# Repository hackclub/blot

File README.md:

# Blot, the plotter bot from Hack Club

**[🕸 Landing Page](https://blot.hackclub.com)** | **[💻 Online Editor](https://blot.hackclub.com/editor)** | **[👀 Gallery](https://blot.hackclub.com/gallery)**

> Saw Blot at [RMRRF](https://rmrrf.com) 2026? That was a fork of the firmware, check it out [here](https://github.com/samdev-7/upgraded-blot).

Create programmatic art in our web-based editor and submit it to the gallery and we'll send you a CNC machine which can make that art for free.
Blot is a [**You Ship, We Ship**](https://github.com/hackclub/blot/tree/main?tab=readme-ov-file#you-ship-we-ship) project from [Hack Club](https://hackclub.com).

> Everything about Blot is open source. The online editor and drawing library can be freely used by anyone, and we encourage all to submit to the gallery through PRs! However, you must be a teenager or younger to receive a free machine.

A piece of art made for Blot can be the first program you ever write, but it can also be a challenge for a master programmer. Check out some of the art made already in our [gallery](https://blot.hackclub.com/gallery). Every piece of art you see is actually a program. Many of them create unique pieces every time the art is run. You may be looking at an artwork which has never been seen before, even by the creator.

For a short video introduction to Blot [check out our 38 second trailer](https://www.youtube.com/watch?v=d1noJNmfvC0).

# How It Works

### 1) Create a piece of programmatic art in the web editor.

To learn the Blot drawing library follow our [getting started guide](https://blot.hackclub.com/editor?guide=start). Check out the examples in the [gallery](https://blot.hackclub.com/gallery) and then follow along with some of our [guides](https://blot.hackclub.com/guides).

### 2) Submit that art to the public gallery.

The [submission rules to get a Blot for a PR are here](https://github.com/hackclub/blot/blob/main/docs/GET_A_BLOT.md). **You must be a teenager (or younger to qualify for a free machine)** but anyone can make art and make a PR.

### 3) Receive the parts to build your own Blot that can draw that art in real life.

The [bill of materials can be found here](/docs/BOM.toml) and an [assembly guide here](https://blot.hackclub.com/assembly).

<!--  -->

# Blot is...

**A custom CNC drawing machine** designed from scratch to introduce you to digital fabrication.
It's made of 6 unique 3D printed parts with a custom control board and easy to understand firmware, which can be interfaced with through JavaScript in the browser.
Blot is designed in OnShape. Check out the [3D model of the project](https://cad.onshape.com/documents/536478c2ac00624edd8e2182/w/945ceabd15096661108b7650/e/61fd4346c9fdab983c6ba24d?renderMode=0&uiState=66980ee799bd766f406eb9c8).
You can find the [bill of materials here](https://blot.hackclub.com/assembly) and, if you'd like to 3D print your Blot, [the parts are here](https://github.com/hackclub/blot/tree/main/hardware/mechanical/drawing-thing-v4). The entire build costs about $150 dollars. If you're a teen we will give you all the parts for a PR with your an art piece you coded yourself.

**A web based editor for programmatic art** that we designed specifically for pen plotting with a [custom geometry library](/docs/DOCUMENTATION.md).
We practiced programmatic pen plotting with [some](https://github.com/LingDong-) [amazing artists](https://static1.squarespace.com/static/63fbc39db5b01b5fa30423db/t/649b424d33b2ce3e0d5b63a5/1687896656015/June+Cohort+Zine.pdf).
There is so much to learn and explore on the programming and the aesthetic side.

# Blot Docs

Here are a collection of resources for Blot:

- [Complete documentation of the drawing library in the editor](https://github.com/hackclub/blot/blob/main/docs/DOCUMENTATION.md)
- [Short documentation shown in the Blot editor](https://github.com/hackclub/blot/blob/main/public/TOOLKIT.md)
- [The Blot assembly and operation guide](https://github.com/hackclub/blot/blob/main/docs/assembly/ASSEMBLY.md)
- [The source of truth bill of materials (BOM)](https://github.com/hackclub/blot/blob/main/docs/BOM.toml)
- [Criteria for how to get a Blot and a guide on how to submit a PR](https://github.com/hackclub/blot/blob/main/docs/GET_A_BLOT.md)
- [A guide on how to review Blot submissions](https://github.com/hackclub/blot/blob/main/docs/BLOT_REVIEW.md)
- [A brief guide on how to approve Blot requests for Blot shipments](https://github.com/hackclub/blot/blob/main/docs/APPROVING_BLOT_REQUESTS.md)
- [Information on how we order Blot supplies from our manufacturing partners](https://github.com/hackclub/blot/blob/main/docs/ORDERING_BLOT_KITS.md)
- [The files for the 3D printed parts](https://github.com/hackclub/blot/tree/main/hardware/mechanical/blot-v6)
- [The source files for the control PCB](https://github.com/hackclub/blot/tree/main/hardware/motor-control-board/circuit/controller)
- [The source files for the power delivery PCB](https://github.com/hackclub/blot/tree/main/hardware/motor-control-board/circuit/power-delivery)
- [The firmware for the Blot control board](https://github.com/hackclub/blot/blob/main/hardware/motor-control-board/firmware/firmware.ino)
- [Sample Blot based lesson plan](https://github.com/hackclub/blot/blob/main/docs/lesson/LESSON-PLAN.md)
- [Video of a Blot being assembled](https://www.youtube.com/watch?v=7N-Nu6_oo4I)
- [Video of operating a Blot](https://www.youtube.com/watch?v=qDP5CNjFHJE)
- [Video of making a Blot submission](https://www.youtube.com/watch?v=AmbjNEPuv14)
- [Video Blot promo trailer](https://www.youtube.com/watch?v=d1noJNmfvC0)
- [Video introduction to JavaScript in the context of Blot](https://www.youtube.com/watch?v=3KAan1PzmxA)
- [Video introduction to Blot editor](https://www.youtube.com/watch?v=OZ9KaFr1V_o)
- [Video demonstrating working through a Blot guide](https://www.youtube.com/watch?v=mP4rUdaF8ng)

# What are People Making with Blot

Blot has been in development since January 2023 and was released April 2024. We've had lots of people use the Blot editor and the Blot machine to create visual art, run workshops and as part of interactive installations. Here's a sense of what can be done with Blot.

### Programmatic Art

There are all sorts of styles of programmatic art. Here are some examples of great Blot submissions that show a range of styles. This list is by no means exhaustive.

**The natural scene** is a common source of artistic inspiration. This could be called figurative or representational art when it tries to depict a real thing with some fidelity. One example are these roots by Kai (age 17).

**The geometric pattern** is natural avenue to pursue when making art with computers because code is a great way to describe patterns. Oz's approach of clipping overlapping segments creates a wonderful sense of depth.

**The tech demo (with composition)** is focusing on a specific technical approach like in Henry's (age 15) ray marcher. The art piece isn't complete though until the artists uses the technique to make a composition.

<a href="https://blot.hackclub.com/editor?src=https://raw.githubusercontent.com/hackclub/blot/main/art/raymarching-henry/index.js">
  <picture>
    <source media="(prefers-color-scheme: dark)" srcset="https://github.com/hackclub/blot/assets/61765149/d65464eb-8cc2-4bf3-be82-0b4cc12070bd">
    <source media="(prefers-color-scheme: light)" srcset="https://github.com/hackclub/blot/assets/27078897/90c01a52-0404-423f-8ae9-763bc591ff9f">
    
  </picture>
</a>

**The data transformation** can be seen in Kieran's (age 15) self portrait. It takes data from an SVG but modifies it programmatically to produce an art piece. This approach could be used to visualize data that may not of been visual to begin with.

**The concept** is important with any artwork and can be mixed with any of the genres above. Ultimately an interesting idea can be what elevates something that is visually pretty simple, one example by Ayush is the Blot's own self portrait.

<a href="https://blot.hackclub.com/editor?src=https://raw.githubusercontent.com/hackclub/blot/main/art/blot-ayush/index.js">
  <picture>
    <source media="(prefers-color-scheme: dark)" srcset="https://github.com/hackclub/blot/assets/61765149/12044cdf-a498-438c-814b-48622488e42f">
    <source media="(prefers-color-scheme: light)" srcset="https://github.com/hackclub/blot/assets/27078897/1f367d9b-aa74-4fca-8623-259a06800335">
    
  </picture>
</a>

For way more examples check out the [gallery](https://blot.hackclub.com/gallery).

### Blot as Creative Material

You ship we ship projects are developed to provide technological creative material. The Blot was developed to not just create visual programs on computers but also to explore robotic and interactive technology. Here are some ways the machine or project has been used to create interactive technology experiences.

[**Lineflow**](https://github.com/leomcelroy/lineflow) was developed as an interactive art piece for an MIT Museum event. Participants would create a single line drawing on the computer and would then watch a simulation of a line folding into their drawing. Three frames of that simulation were strung together to create a timeline of the animation that would be drawn by a Blot to be brought home by the participant.

**The infinite gallery** at [Outernet](https://www.youtube.com/watch?v=O1s5HqSqKi0) (Hack Club's 2023 summer hackathon). Leo, Kai, and Henry constructed a black out box that contained an infinite art gallery. Participant's entered a room sized black box with one wall illuminated with artwork and a giant joystick in the center. They could navigate the gallery with the joystick and as they explored new (possibly never before seen) art was generated based on their location.

**Chinese calligraphy workshop** was developed for and run at the [Hack Club leader summit 2024](https://www.youtube.com/watch?v=UZEm5lONg7g) by Bright Li (age 15). During it participants learned how to draw Chinese calligraphy programmatically and then handed ink brushes to Bright's Blot robot to put the drawings to the page.

# It's All Open Source

Every part of Blot is freely available for you to investigate and discover.
That includes the editor, the hardware design, the electronics, and even the finances around the project.
We think people deserve tools they can take ownership of. That's why we give away the source for free.

Our projects at Hack Club have hundreds of teenage contributors from all over the world. If you want to learn how to program, we invite you to jump in and start building tools used by thousands.

You're also welcome to participate and use our tools if you aren't a teen (like making art or building your own blot), but our [online community](https://hackclub.com/slack) is for teens only.

# You Ship, We Ship

At Hack Club we're reimagining a new type of public education for technology. We believe people learn best by creating things they care about and sharing them with others. We build open source creative tools with young people all around the world. These tools are gateways to new subjects in technology like [embedded systems](https://sprig.hackclub.com), [circuits](https://onboard.hackclub.com) or digital fabrication robotics. When teenagers build things with our tools we send them more creative materials for free.

Our goal is to build a new type of library online that offers learners not just media to consume but tools to create. And it is free and open source to all. We're just getting started...

# Development

Join the `#blot` channel on the [Hack Club Slack](https://hackclub.com/slack).

The Blot editor is run with an Express server.

After installing `Git`, `Node.js`, and `Yarn`, clone the repo.

```
git clone https://github.com/hackclub/blot/
yarn install
```

To run the development server:

```
yarn dev
```

# License

The Hack Club Blot is open source and licensed under the [MIT License](https://github.com/hackclub/blot/LICENSE.md). Fork, remix, and make it your own! Pull requests and other contributions greatly appreciated.

# Acknowledgements

Many people have contributed to Blot, to mention a few and give much thanks too...

MIT's Center for Bits and Atoms for providing expert advice and occasionally a space to work.

Sam Hu and his team at ISourceAsia for supplying Blot parts and becoming a critical part of the Blot team.

Paul Hamilton for his contributions to embedded circuit designs.

Oz Nova for writing an excellent getting started guide.

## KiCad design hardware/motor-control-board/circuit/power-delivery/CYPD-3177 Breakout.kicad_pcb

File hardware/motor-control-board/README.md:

# Blot Control Board

The assembled blot control board is a main board with a set of smaller boards attached to it's headers:

- 1x Blot Control Board ([designed in house](./circuit/controller/))
    - 2x A4988 stepper motor drivers
    - 1x Seeeduino XIAO RP2040
    - 1x USB-C Power Delivery board ([designed in house](./circuit/power-delivery/))
    - 1x Stepper motor breakout board ([designed in house](./circuit/stepper-motor-headers/))

The KiCAD project files are provided in the repo and are designed with KiCAD v7. This may not be compatible with previous versions, but you can get the latest version [here](https://www.kicad.org/download/). 

## Carrier Board

The carrier board wires the breakouts together, provides external power circuitry for the A4988 and steppers, and a convenient way to mount the board to the blot machine. It's a simple 2-layer 1.6mm PCB measured at 50x70mm. It also has a pin header breaking out 5 unused GPIO pins, including 1 DAC channel, 2 analog-capable pins, and one I2C bus. 

## Power Delivery Board

The power delivery board provides a fixed output of 9V1A using the CYPD3177 chipset. It's highly flexible, allowing USB-C Charging up to 15W and USB-C PD up to 100W. Unlike many other chips available, it does not require any firmware nor flashing, and power settings are configured with pullup and pulldown resistors. This board is set to 9V @ 1A, to ensure maximum compatibility with most PD-capable bricks. It's very compact, measuring less than 22x32mm with breadboard-friendly mounting, an affordable 2-layer design, and single side SMD component placement. 

During prototyping, we used an off-the-shelf module from Amazon. These only had four 2.54mm pins on the edge of the board and were hard to mount onto the board securely. Building our own also gave us better control over supply of these boards. 

*As a precaution: while this board is breadboard friendly, typical solderless breadboards are only rated up to _5V @ 1A_. Do _not_ use this on a solderless breadboard.*

## Additional Relevant Reading

Below is a list of datasheets / product briefs that may be relevant. 

[Seeeduino RP2040 XIAO](https://wiki.seeedstudio.com/XIAO-RP2040/)\
[A4988 Breakout Board](https://www.pololu.com/product/1182)\
[CYPD3177](https://www.infineon.com/cms/en/product/universal-serial-bus/usb-c-charging-port-controllers/ez-pd-barrel-connector-replacement-bcr/cypd3177-24lqxq/)\
[DMP3013SFV](https://www.diodes.com/assets/Datasheets/DMP3013SFV.pdf)\
[MM3Z15VC](https://www.onsemi.com/pdf/datasheet/mm3z9v1c-d.pdf)\
[WCAP-ATG5](https://www.we-online.com/components/products/datasheet/860020573008.pdf)\
[JS Series Switch](https://www.ckswitches.com/media/1422/js.pdf)\
[Schottky Diode](https://datasheets.kyocera-avx.com/schottky.pdf)

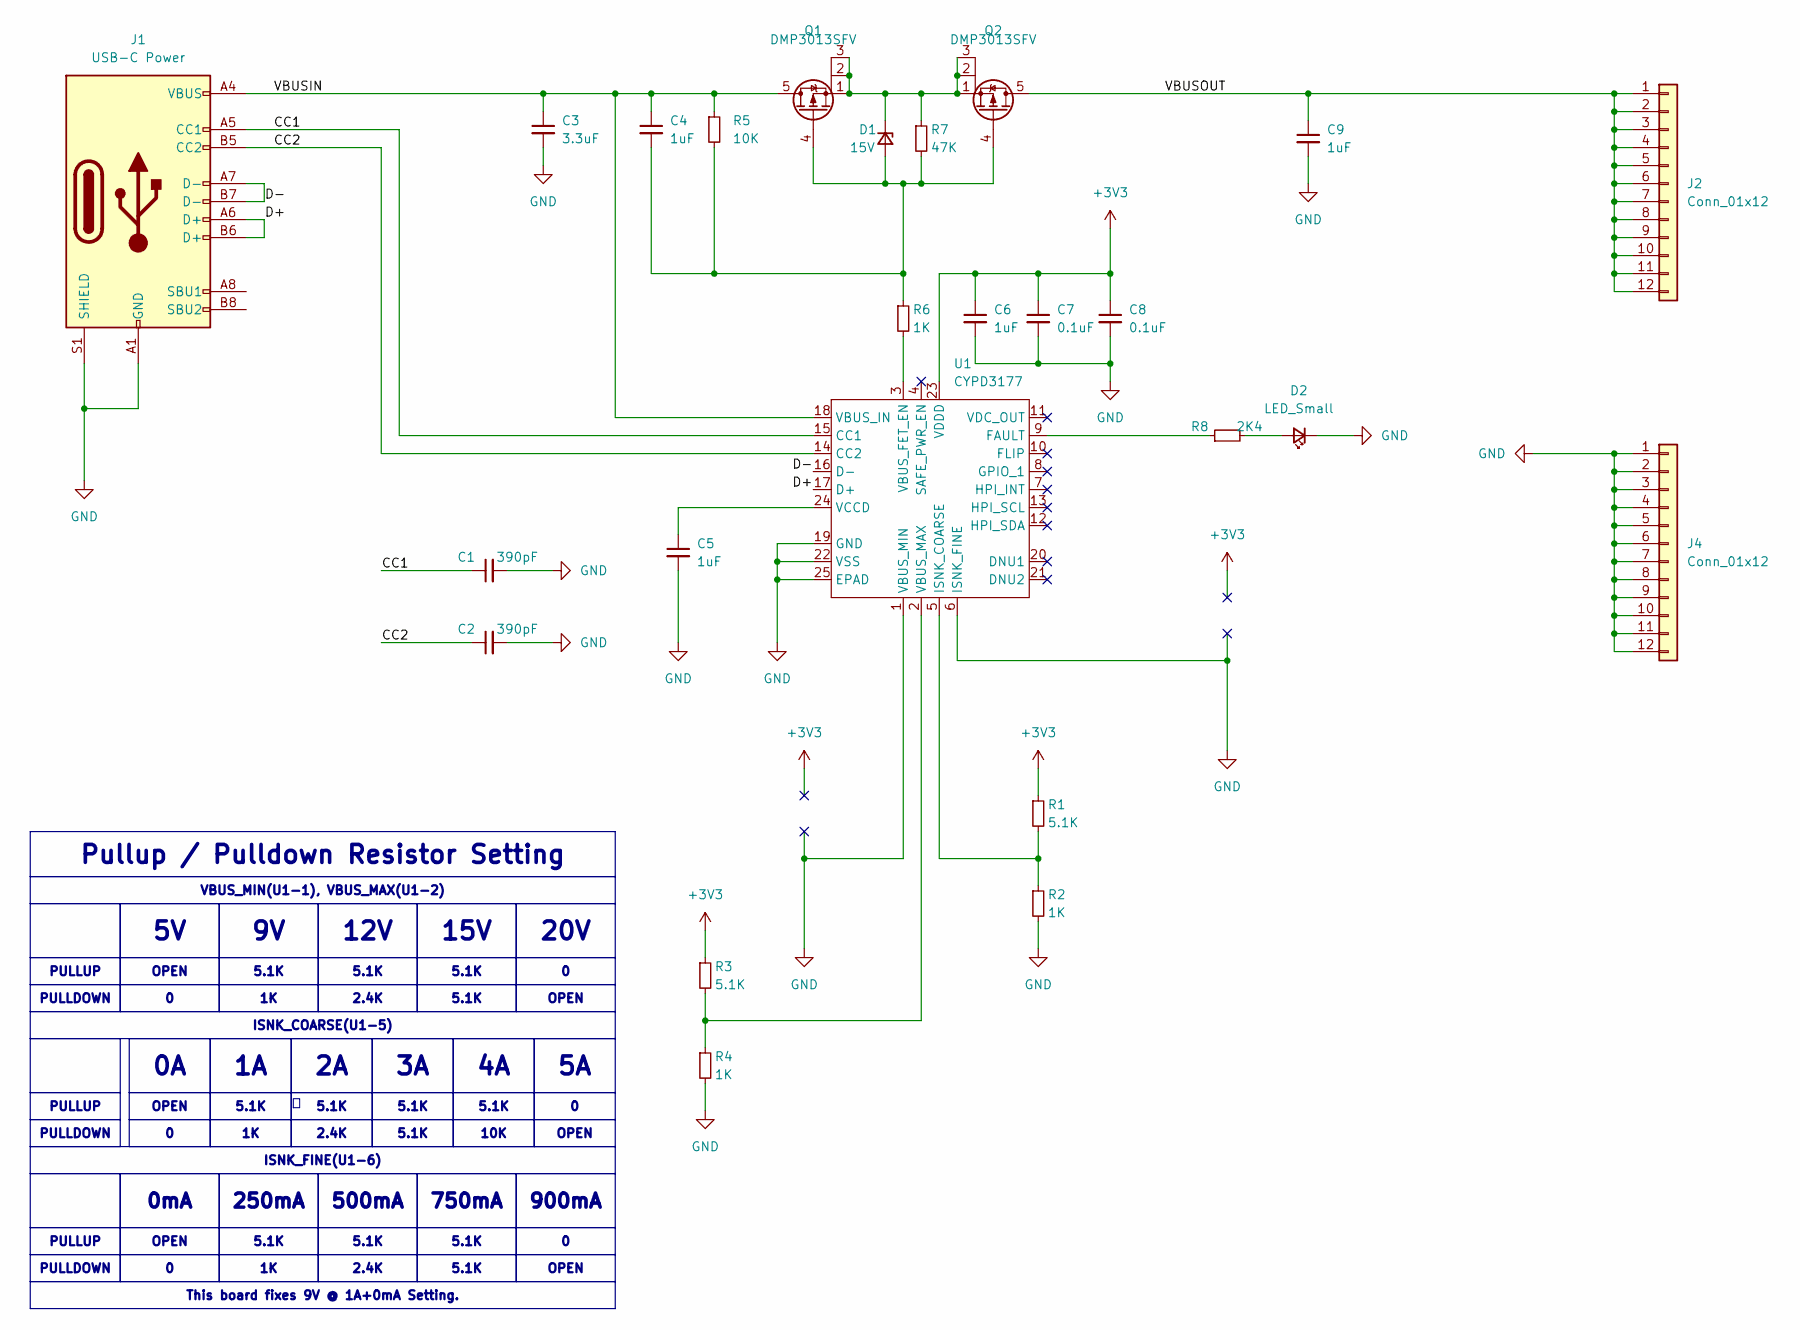
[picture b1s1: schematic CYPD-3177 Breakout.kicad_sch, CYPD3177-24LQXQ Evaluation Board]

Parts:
C1, C2: 390pF; C_0603_1608Metric_Pad1.08x0.95mm_HandSolder
C3: 3.3uF; C_0805_2012Metric_Pad1.18x1.45mm_HandSolder
C4, C5, C6, C9: 1uF; C_0603_1608Metric_Pad1.08x0.95mm_HandSolder
C7, C8: 0.1uF; C_0603_1608Metric_Pad1.08x0.95mm_HandSolder
D1: 15V; D_SOD-323F
D2: LED_Small; LED_0805_2012Metric_Pad1.15x1.40mm_HandSolder
J1: USB-C Power; USB_C_Receptacle_HRO_TYPE-C-31-M-12
J2, J4: Conn_01x12; PinHeader_1x12_P2.54mm_Vertical
Q1, Q2: DMP3013SFV; Diodes_PowerDI3333-8
R1, R3: 5.1K; R_0603_1608Metric_Pad0.98x0.95mm_HandSolder
R2, R4, R6: 1K; R_0603_1608Metric_Pad0.98x0.95mm_HandSolder
R5: 10K; R_0603_1608Metric_Pad0.98x0.95mm_HandSolder
R7: 47K; R_0603_1608Metric_Pad0.98x0.95mm_HandSolder
R8: 2K4; R_0603_1608Metric_Pad0.98x0.95mm_HandSolder
U1: CYPD3177; QFN-24-1EP_4x4mm_P0.5mm_EP2.7x2.7mm

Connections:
+3V3: C6.1, C7.1, C8.1, R1.1, R3.1, U1.23 (VDDD)
/CC1: C1.1, J1.A5 (CC1), U1.15 (CC1)
/CC2: C2.1, J1.B5 (CC2), U1.14 (CC2)
/D+: J1.A6 (D+), J1.B6 (D+), U1.17 (D+)
/D-: J1.A7 (D-), J1.B7 (D-), U1.16 (D-)
/VBUSIN: C3.1, C4.1, J1.A4 (VBUS), J1.A9 (VBUS), J1.B4 (VBUS), J1.B9 (VBUS), Q1.5 (D), R5.1, U1.18 (VBUS_IN)
/VBUSOUT: C9.1, J2.1, J2.2, J2.3, J2.4, J2.5, J2.6, J2.7, J2.8, J2.9, J2.10, J2.11, J2.12, Q2.5 (D)
GND: C1.2, C2.2, C3.2, C5.2, C6.2, C7.2, C8.2, C9.2, D2.1 (K), J1.A1 (GND), J1.A12 (GND), J1.B1 (GND), J1.B12 (GND), J1.S1 (SHIELD), J4.1, J4.2, J4.3, J4.4, J4.5, J4.6, J4.7, J4.8, J4.9, J4.10, J4.11, J4.12, R2.2, R4.2, U1.1 (VBUS_MIN), U1.6 (ISNK_FINE), U1.19 (GND), U1.22 (VSS), U1.25 (EPAD)
unnamed: C4.2, D1.2 (A), Q1.4 (G), Q2.4 (G), R5.2, R6.1, R7.2
unnamed: D1.1 (K), Q1.1 (S), Q1.2 (S), Q1.3, Q2.1 (S), Q2.2, Q2.3 (S), R7.1
unnamed: D2.2 (A), R8.2
unnamed: R8.1, U1.9 (FAULT)
unnamed: R1.2, R2.1, U1.5 (ISNK_COARSE)
unnamed: R6.2, U1.3 (VBUS_FET_EN)
unnamed: R3.2, R4.1, U1.2 (VBUS_MAX)
unnamed: C5.1, U1.24 (VCCD)

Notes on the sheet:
20V
5.1K
ISNK_COARSE(U1-5)
2.4K
0mA
VBUS_MIN(U1-1), VBUS_MAX(U1-2)
500mA
OPEN
OPEN
10K
15V
This board fixes 9V @ 1A+0mA Setting.
PULLDOWN
12V
250mA
PULLUP
900mA
Pullup / Pulldown Resistor Setting
750mA
ISNK_FINE(U1-6)

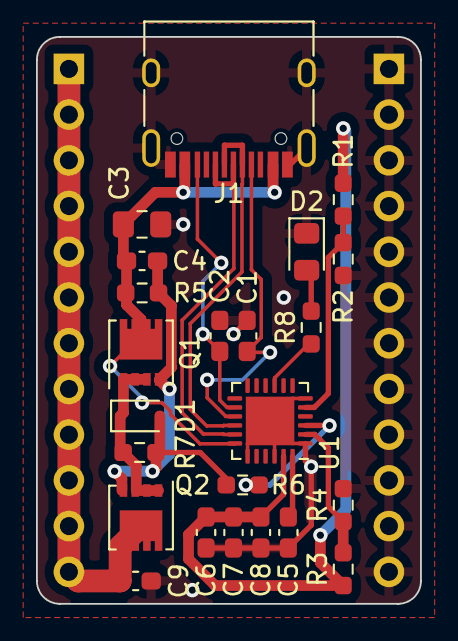
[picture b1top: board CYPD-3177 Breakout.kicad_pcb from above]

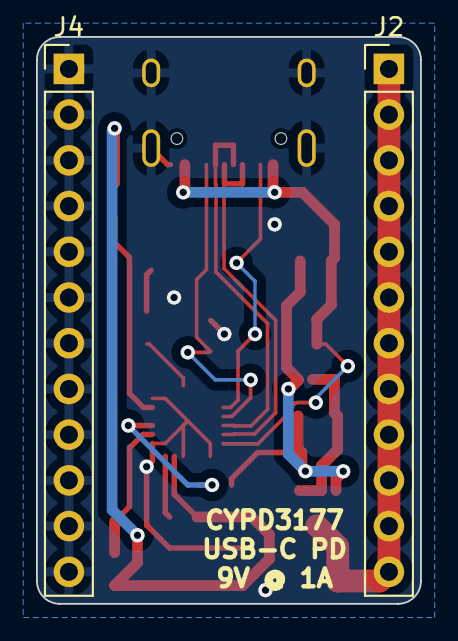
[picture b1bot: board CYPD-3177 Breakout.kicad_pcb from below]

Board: 2 copper layers, 21.3 x 31.5 mm, 25 parts (2 on the bottom side), 16 nets.

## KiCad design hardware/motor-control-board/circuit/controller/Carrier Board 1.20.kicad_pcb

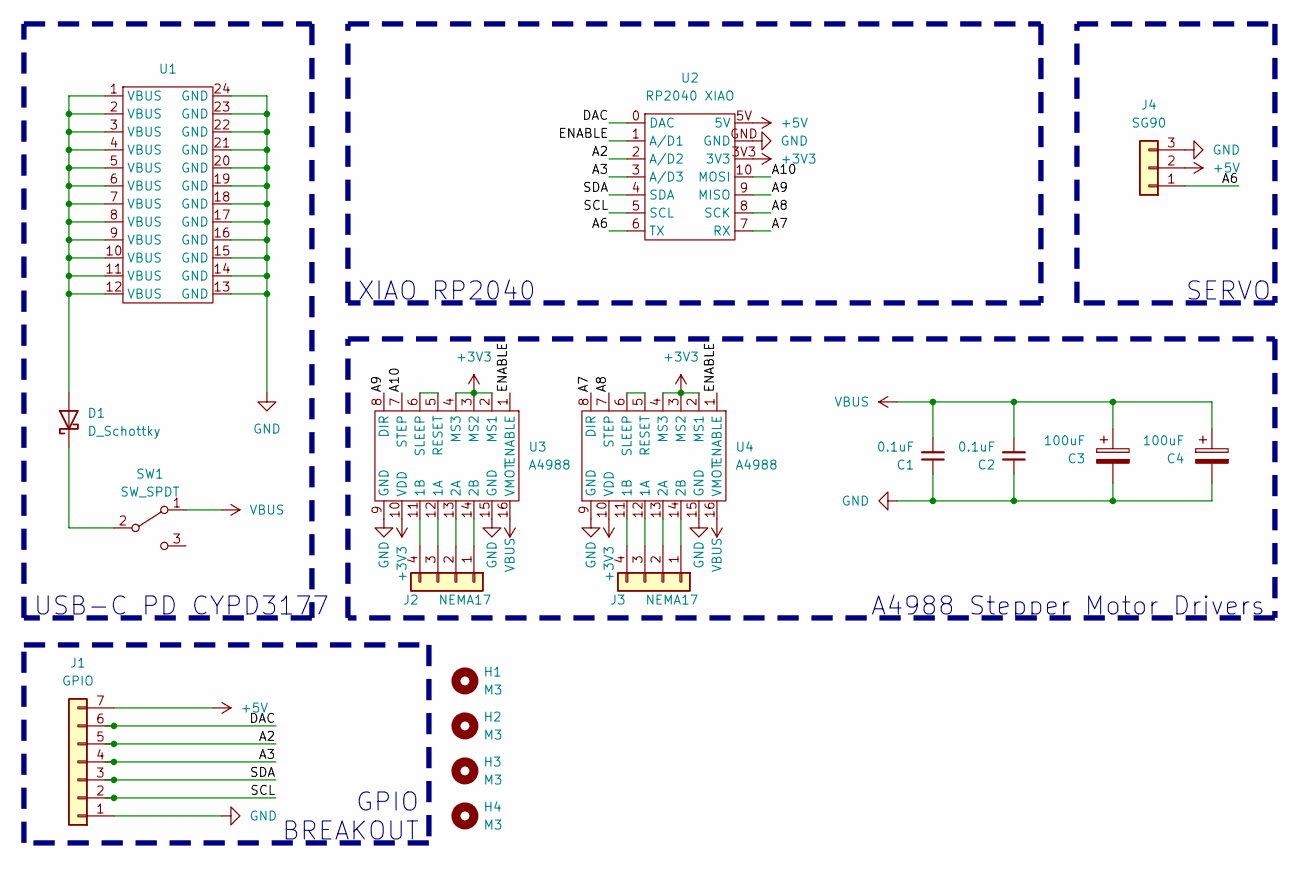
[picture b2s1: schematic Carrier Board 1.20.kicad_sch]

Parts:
C1, C2: 0.1uF; C_0805_2012Metric_Pad1.18x1.45mm_HandSolder
C3, C4: 100uF; CP_Radial_D6.3mm_P2.50mm
D1: D_Schottky; D_1206_3216Metric_Pad1.42x1.75mm_HandSolder
H1, H2, H3, H4: M3; MountingHole_3.2mm_M3
J1: GPIO; PinSocket_1x07_P2.54mm_Vertical
J2, J3: NEMA17; PinHeader_1x04_P2.54mm_Vertical
J4: SG90; PinHeader_1x03_P2.54mm_Vertical
SW1: SW_SPDT; SWITCH_011CQN
U1: USB-C PD
U2: RP2040 XIAO; QTPYXIAORP2040
U3, U4: A4988

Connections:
+3V3: U2.3V3, U3.2 (MS1), U3.3 (MS2), U3.4 (MS3), U3.10 (VDD), U4.2 (MS1), U4.3 (MS2), U4.4 (MS3), U4.10 (VDD)
+5V: J1.7, J4.2, U2.5V
/A2: J1.5, U2.2 (A/D2)
/A3: J1.4, U2.3 (A/D3)
/A6: J4.1, U2.6 (TX)
/A7: U2.7 (RX), U4.8 (DIR)
/A8: U2.8 (SCK), U4.7 (STEP)
/A9: U2.9 (MISO), U3.8 (DIR)
/A10: U2.10 (MOSI), U3.7 (STEP)
/DAC: J1.6, U2.0 (DAC)
/ENABLE: U2.1 (A/D1), U3.1 (ENABLE), U4.1 (ENABLE)
/SCL: J1.2, U2.5 (SCL)
/SDA: J1.3, U2.4 (SDA)
GND: C1.1, C2.1, C3.2, C4.2, J1.1, J4.3, U1.13 (GND), U1.14 (GND), U1.15 (GND), U1.16 (GND), U1.17 (GND), U1.18 (GND), U1.19 (GND), U1.20 (GND), U1.21 (GND), U1.22 (GND), U1.23 (GND), U1.24 (GND), U2.GND, U3.9 (GND), U3.15 (GND), U4.9 (GND), U4.15 (GND)
unnamed: D1.2 (A), U1.1 (VBUS), U1.2 (VBUS), U1.3 (VBUS), U1.4 (VBUS), U1.5 (VBUS), U1.6 (VBUS), U1.7 (VBUS), U1.8 (VBUS), U1.9 (VBUS), U1.10 (VBUS), U1.11 (VBUS), U1.12 (VBUS)
unnamed: D1.1 (K), SW1.2 (B)
unnamed: J2.1, U3.14 (2B)
unnamed: J2.2, U3.13 (2A)
unnamed: J2.3, U3.12 (1A)
unnamed: J2.4, U3.11 (1B)
unnamed: J3.1, U4.14 (2B)
unnamed: J3.2, U4.13 (2A)
unnamed: J3.3, U4.12 (1A)
unnamed: J3.4, U4.11 (1B)
unnamed: U3.5 (RESET), U3.6 (SLEEP)
unnamed: U4.5 (RESET), U4.6 (SLEEP)
VBUS: C1.2, C2.2, C3.1, C4.1, SW1.1 (A), U3.16 (VMOT), U4.16 (VMOT)

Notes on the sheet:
USB-C PD CYPD3177
SERVO
A4988 Stepper Motor Drivers
XIAO RP2040
GPIO BREAKOUT

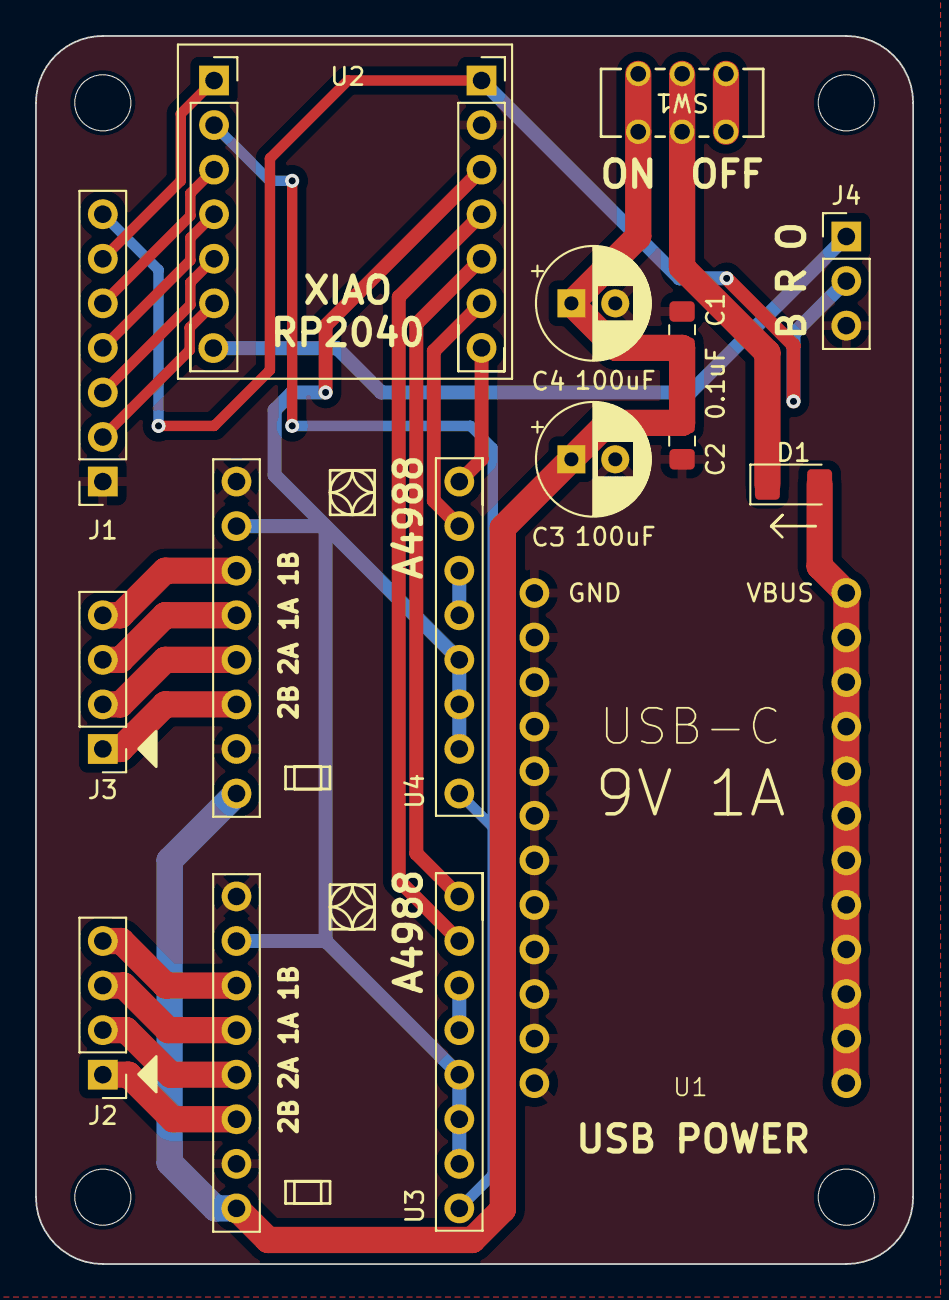
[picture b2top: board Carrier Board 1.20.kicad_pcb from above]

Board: 2 copper layers, 50.0 x 70.0 mm, 18 parts (0 on the bottom side), 27 nets.

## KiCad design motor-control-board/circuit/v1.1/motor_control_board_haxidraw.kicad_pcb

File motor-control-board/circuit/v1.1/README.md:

This is a slight revision based off the original board under the main circuit folder. A few key distinctions:
- created in KiCAD, not SVGPCB
- has alternative power input options: such as a screw terminal and test points. 
- some silkscreen markings, particularly around power and servo.

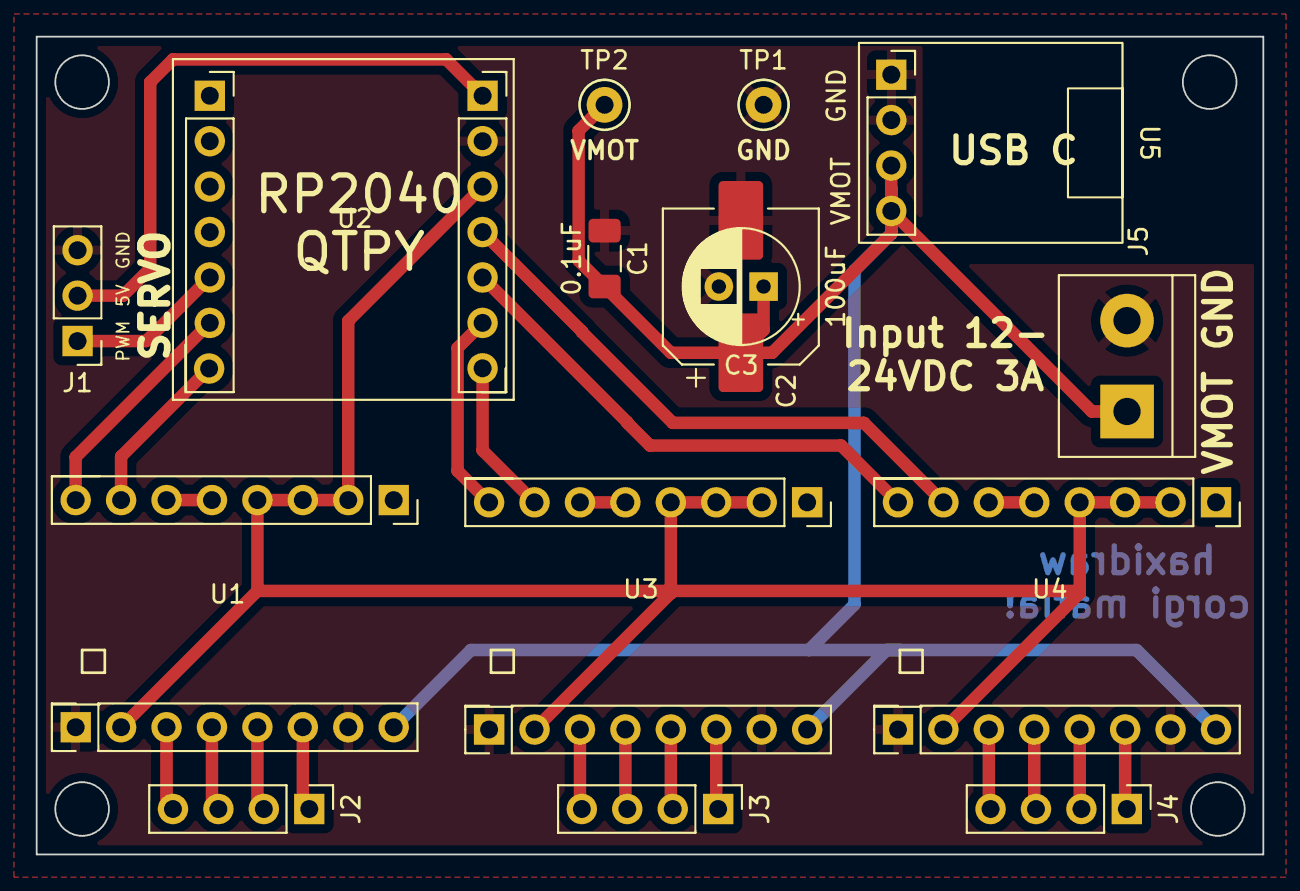
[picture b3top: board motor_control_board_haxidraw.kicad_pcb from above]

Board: 2 copper layers, 68.6 x 45.7 mm, 15 parts (0 on the bottom side), 26 nets.

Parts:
C1: 0.1uF; C_1206_3216Metric_Pad1.33x1.80mm_HandSolder
C2: 100uF; CP_Elec_8x10.5
C3: 100uF DNP; CP_Radial_D6.3mm_P2.50mm
J1: Conn_01x03; PinHeader_1x03_P2.54mm_Vertical
J2, J3, J4: Conn_01x04; PinHeader_1x04_P2.54mm_Vertical
J5: Screw_Terminal_01x02; TerminalBlock_bornier-2_P5.08mm
TP1, TP2: TestPoint; TestPoint_Keystone_5000-5004_Miniature
U1, U3, U4: A4988
U2: QTPY/XIAO_RP2040; QTPYXIAORP2040
U5: USBC_PD; usbcPD

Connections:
+3V3: U1.2 (MS1), U1.3 (MS2), U1.4 (MS3), U1.10 (VDD), U2.3V3, U3.2 (MS1), U3.3 (MS2), U3.4 (MS3), U3.10 (VDD), U4.2 (MS1), U4.3 (MS2), U4.4 (MS3), U4.10 (VDD)
+5V: J1.2, U2.5V
A7: U2.7 (RX), U3.7 (STEP)
A8: U2.8 (SCK), U3.8 (DIR)
A9: U2.9 (MISO), U4.8 (DIR)
A10: U2.10 (MOSI), U4.7 (STEP)
GND: C1.1, C2.2, C3.2, J1.3, J5.2, TP1.1, U1.9 (GND), U1.15 (GND), U2.GND, U3.9 (GND), U3.15 (GND), U4.9 (GND), U4.15 (GND), U5.1 (-), U5.2 (-)
unnamed: J1.1, U2.4 (SDA)
unnamed: J2.1, U1.14 (2B)
unnamed: J2.2, U1.13 (2A)
unnamed: J2.3, U1.12 (1A)
unnamed: J2.4, U1.11 (1B)
unnamed: J3.1, U3.14 (2B)
unnamed: J3.2, U3.13 (2A)
unnamed: J3.3, U3.12 (1A)
unnamed: J3.4, U3.11 (1B)
unnamed: J4.1, U4.14 (2B)
unnamed: J4.2, U4.13 (2A)
unnamed: J4.3, U4.12 (1A)
unnamed: J4.4, U4.11 (1B)
unnamed: U1.5 (RESET), U1.6 (SLEEP)
unnamed: U1.7 (STEP), U2.6 (TX)
unnamed: U1.8 (DIR), U2.5 (SCL)
unnamed: U3.5 (RESET), U3.6 (SLEEP)
unnamed: U4.5 (RESET), U4.6 (SLEEP)
VMOT: C1.2, C2.1, C3.1, J5.1, TP2.1, U1.16 (VMOT), U3.16 (VMOT), U4.16 (VMOT), U5.3 (+), U5.4 (+)

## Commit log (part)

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2024-09-07 Rename image (2).png to pic1.png
2024-09-07 pic2 new
2024-09-07 Rename image (3).png to pic2.png
2024-09-07 Rename image (4).png to pic3.png
2024-09-07 Rename pic1.png.png to pic1.png
2024-09-07 Rename pic2.png.png to pic2.png
2024-09-07 Rename pic3.png.png to pic3.png
2024-09-08 add description and wikipedia link
2024-09-08 faces
2024-09-08 clouds
2024-09-09 fixed folders
2024-09-09 Update Image_to_array_coverter.html
    making max height and width 125
2024-09-10 Update art
2024-09-10 Updated LineyPeaks to v2
2024-09-14 Add spirals, random seed, diverse sizing, and depth enhancement
2024-09-15 upload
2024-09-17 Rename art/PasswordGen/Screenshot 2024-09-16 192418.png to art/PasswordGen/Snapshots/Snapshot0
2024-09-17 Rename art/PasswordGen/Screenshot 2024-09-16 192510.png to art/PasswordGen/Snapshots/Snapshot1
2024-09-17 Rename art/PasswordGen/Screenshot 2024-09-16 192534.png to art/PasswordGen/Snapshots/snapshot2
2024-09-17 yipeeeee
2024-09-23 Add star shapes to background pattern
2024-09-23 Make the frequency & name pull from repeaterbook
2024-09-23 Add an explanation of everything
2024-09-23 Add some more comments
2024-09-24 yay final please please please please please
2024-09-25 fix: error in ASSEMBLY.md
2024-09-25 added iceburgs + scarfs + made em rotate + made em more "penguin-like"
2024-09-26 Rename project.js to index.js
2024-09-30 lorenz-omay
2024-10-01 marchingsquares-omay
2024-10-02 Update index.js
    Made the hair and eyes move randomly
2024-10-02 Nidhir
2024-10-02 Added file
2024-10-02 added my blot
2024-10-06 Fix circle generation to stay within drawable bounds
2024-10-07 starseed-sahandSoleimani
2024-10-08 contained the lines a bit more
2024-10-08 added a parameter for the cutoff
2024-10-08 forgot to change from local -> blot editor
2024-10-08 Update index.js
    - Made it a box of cupcakes rather than just 1
    - Cupcake drawing is function-driven, with custom placement and size
    - Color cupcake looks better (doesn't use outline color)
    - Debug tools using text printing (useful in school when I don't have access to console)
    - Use actual collision detection rather than just trying to guess using circles
2024-10-08 Update index.js
    - Make color cupcakes actually work in box
2024-10-08 - Edit screenshots to show updates
2024-10-09 Rename snapshot0.png to art/Wireframe-tunnel-Matthew/snapshot0.png
2024-10-09 Rename Wireframe-tunnel-Matthew/index.js to art/Wireframe-tunnel-Matthew/index.js
2024-10-09 Add "Isometric Madness"
2024-10-09 Update "IsometricMadness" - replace Math.random()
2024-10-09 Update "IsometricMadness" - fix file name
2024-10-09 Update "IsometricMadness" - delete broken screenshot
2024-10-11 Added some text in the bottom!
2024-10-14 added submission
2024-10-14 fixed submission
2024-10-15 Create snowMelt-elijahPierce
2024-10-16 Add sheetMusicGenerator
2024-10-16 Forgot to update with the new script
2024-10-16 Add logic for clef
2024-10-16 Rename to index.js
2024-10-16 randomly generates emojy each time
2024-10-16 fixed overlapping
2024-10-17 Fix stems again
2024-10-17 Update images
2024-10-17 added a sky!
2024-10-18 Rename Forget.jpg to Forget.jpg
2024-10-18 Rename index.js to index.js
2024-10-27 Add Circuit_WFC-Hitu
2024-10-30 Added MusicUI
2024-10-30 Add Decorations
    Add sticker
    Add background cupcakes
    Add line decorations
2024-10-30 Update Snapshots
2024-11-02 Updated with bowl
2024-11-02 Accidental misname! Deleting and recommitting
2024-11-02 Uploaded bowl project
2024-11-13 Create snapshots directory
2024-11-13 Create dir
2024-11-13 Randomize heart shape and reduce circle overlap
2024-11-14 Update and rename project.js to index.js
    new code updates
2024-11-14 moved project to art folder
2024-11-15 add another demo (has all features)
2024-11-15 Update sharding
2024-11-15 Update index.js
    added cloud and sun and stuff
2024-11-18 centered fractions
2024-11-18 Create new directory
2024-11-19 Update index.js
    got rid of fill
2024-11-19 Refactor heart generation to use consistent random parameters
    - Replace Math.random() with bt.rand() for seed generation
    - Move heart equation parameters (a-e) to be calculated once at start
2024-11-20 wireframe sphere!
2024-11-21 Update ASSEMBLY.md
    Made various changes:
    - Some steps I found when I was building the blot were mistyped or missing
    - Added a couple debugging tips so people can learn from my failures
2024-11-21 Update PULL_REQUEST_TEMPLATE.md
    Specify that it's not only color, but also the fill option as a whole that doesn't work on blot.
2024-11-23 Create d
2024-11-23 done
2024-11-24 done ig
2024-11-25 Add power switch clarification to ASSEMBLY.md
2024-11-27 Update index.js
    following the instructions I received I have:
    -removed at least 90% of the rando generations that returned an unrealizable drawing
    -fixed the error that occurs during execution
    -corrected the size of the main star so that it is always larger than the others.
    -I don't add details to the planet, but I added the feature of generating some circular stars.
2024-11-28 Update index.js
    Added curved cupcake case as requested
2024-11-28 added curved cupcake case
2024-11-28 center spiral
2024-11-28 clean up code
2024-12-01 Create index
2024-12-11 sunset blot
2024-12-13 Revert "image-to-blot"
2024-12-21 Add Index.js for Code
2024-12-21 Create s
2024-12-28 Update Starry Night
2024-12-29 Update Build Folder
2025-01-06 Removed sticker button
2025-01-08 Update index.js
    added stem to flower, made the petals symmetrical
2025-01-08 added snapshots
2025-01-27 added workflow to auto ocmment
2025-03-31 Update ASSEMBLY.md (fixed broken link to BOM)
2025-06-08 Files added
2026-04-01 Bump nanoid from 5.0.5 to 5.0.9
    Bumps [nanoid](https://github.com/ai/nanoid) from 5.0.5 to 5.0.9.
    - [Release notes](https://github.com/ai/nanoid/releases)
    - [Changelog](https://github.com/ai/nanoid/blob/main/CHANGELOG.md)
    - [Commits](https://github.com/ai/nanoid/compare/5.0.5...5.0.9)
    ---
    updated-dependencies:
2026-04-01 Bump cross-spawn from 7.0.3 to 7.0.6
    Bumps [cross-spawn](https://github.com/moxystudio/node-cross-spawn) from 7.0.3 to 7.0.6.
    - [Changelog](https://github.com/moxystudio/node-cross-spawn/blob/master/CHANGELOG.md)
    - [Commits](https://github.com/moxystudio/node-cross-spawn/compare/v7.0.3...v7.0.6)
    ---
    updated-dependencies:
    - dependency-name: cross-spawn
2026-04-01 Bump express from 4.18.2 to 4.22.0
    Bumps [express](https://github.com/expressjs/express) from 4.18.2 to 4.22.0.
    - [Release notes](https://github.com/expressjs/express/releases)
    - [Changelog](https://github.com/expressjs/express/blob/4.22.0/History.md)
    - [Commits](https://github.com/expressjs/express/compare/4.18.2...4.22.0)
    ---
    updated-dependencies:
2026-04-08 Bump vite from 4.4.9 to 6.4.2 in /virtual-gallery
    Bumps [vite](https://github.com/vitejs/vite/tree/HEAD/packages/vite) from 4.4.9 to 6.4.2.
    - [Release notes](https://github.com/vitejs/vite/releases)
    - [Changelog](https://github.com/vitejs/vite/blob/v6.4.2/packages/vite/CHANGELOG.md)
    - [Commits](https://github.com/vitejs/vite/commits/v6.4.2/packages/vite)
    ---
    updated-dependencies:
2026-04-09 Bump axios from 1.6.7 to 1.15.0 in /headless-blot
    Bumps [axios](https://github.com/axios/axios) from 1.6.7 to 1.15.0.
    - [Release notes](https://github.com/axios/axios/releases)
    - [Changelog](https://github.com/axios/axios/blob/v1.x/CHANGELOG.md)
    - [Commits](https://github.com/axios/axios/compare/v1.6.7...v1.15.0)
    ---
    updated-dependencies:
2026-04-14 Bump follow-redirects from 1.15.5 to 1.16.0
    Bumps [follow-redirects](https://github.com/follow-redirects/follow-redirects) from 1.15.5 to 1.16.0.
    - [Release notes](https://github.com/follow-redirects/follow-redirects/releases)
    - [Commits](https://github.com/follow-redirects/follow-redirects/compare/v1.15.5...v1.16.0)
    ---
    updated-dependencies:
    - dependency-name: follow-redirects
2026-04-14 Bump follow-redirects from 1.15.5 to 1.16.0 in /headless-blot
    Bumps [follow-redirects](https://github.com/follow-redirects/follow-redirects) from 1.15.5 to 1.16.0.
    - [Release notes](https://github.com/follow-redirects/follow-redirects/releases)
    - [Commits](https://github.com/follow-redirects/follow-redirects/compare/v1.15.5...v1.16.0)
    ---
    updated-dependencies:
    - dependency-name: follow-redirects
2026-04-20 Update README.md for clarity and formatting improvements
2026-04-20 Tighten RMRRF fork note wording
2026-05-05 Bump axios from 1.6.7 to 1.16.0 in /headless-blot
    Bumps [axios](https://github.com/axios/axios) from 1.6.7 to 1.16.0.
    - [Release notes](https://github.com/axios/axios/releases)
    - [Changelog](https://github.com/axios/axios/blob/v1.x/CHANGELOG.md)
    - [Commits](https://github.com/axios/axios/compare/v1.6.7...v1.16.0)
    ---
    updated-dependencies:
2026-05-19 Bump ws from 8.16.0 to 8.20.1
    Bumps [ws](https://github.com/websockets/ws) from 8.16.0 to 8.20.1.
    - [Release notes](https://github.com/websockets/ws/releases)
    - [Commits](https://github.com/websockets/ws/compare/8.16.0...8.20.1)
    ---
    updated-dependencies:
    - dependency-name: ws
2026-05-29 Bump axios from 1.6.7 to 1.16.1 in /headless-blot
    Bumps [axios](https://github.com/axios/axios) from 1.6.7 to 1.16.1.
    - [Release notes](https://github.com/axios/axios/releases)
    - [Changelog](https://github.com/axios/axios/blob/v1.x/CHANGELOG.md)
    - [Commits](https://github.com/axios/axios/compare/v1.6.7...v1.16.1)
    ---
    updated-dependencies:
2026-06-04 Bump axios from 1.6.7 to 1.17.0 in /headless-blot
    Bumps [axios](https://github.com/axios/axios) from 1.6.7 to 1.17.0.
    - [Release notes](https://github.com/axios/axios/releases)
    - [Changelog](https://github.com/axios/axios/blob/v1.x/CHANGELOG.md)
    - [Commits](https://github.com/axios/axios/compare/v1.6.7...v1.17.0)
    ---
    updated-dependencies:
2026-06-13 Bump esbuild from 0.20.0 to 0.28.1
    Bumps [esbuild](https://github.com/evanw/esbuild) from 0.20.0 to 0.28.1.
    - [Release notes](https://github.com/evanw/esbuild/releases)
    - [Changelog](https://github.com/evanw/esbuild/blob/main/CHANGELOG-2024.md)
    - [Commits](https://github.com/evanw/esbuild/compare/v0.20.0...v0.28.1)
    ---
    updated-dependencies:
2026-06-15 Bump ws from 7.5.9 to 7.5.11 in /headless-blot
    Bumps [ws](https://github.com/websockets/ws) from 7.5.9 to 7.5.11.
    - [Release notes](https://github.com/websockets/ws/releases)
    - [Commits](https://github.com/websockets/ws/compare/7.5.9...7.5.11)
    ---
    updated-dependencies:
    - dependency-name: ws
2026-06-17 Bump ws from 8.16.0 to 8.21.0
    Bumps [ws](https://github.com/websockets/ws) from 8.16.0 to 8.21.0.
    - [Release notes](https://github.com/websockets/ws/releases)
    - [Commits](https://github.com/websockets/ws/compare/8.16.0...8.21.0)
    ---
    updated-dependencies:
    - dependency-name: ws
2026-06-20 Bump @babel/core from 7.23.9 to 7.29.7
    Bumps [@babel/core](https://github.com/babel/babel/tree/HEAD/packages/babel-core) from 7.23.9 to 7.29.7.
    - [Release notes](https://github.com/babel/babel/releases)
    - [Changelog](https://github.com/babel/babel/blob/main/CHANGELOG.md)
    - [Commits](https://github.com/babel/babel/commits/v7.29.7/packages/babel-core)
    ---
    updated-dependencies:
